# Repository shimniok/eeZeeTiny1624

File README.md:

# eeZeeTiny1624
Developer board for ATtiny1624

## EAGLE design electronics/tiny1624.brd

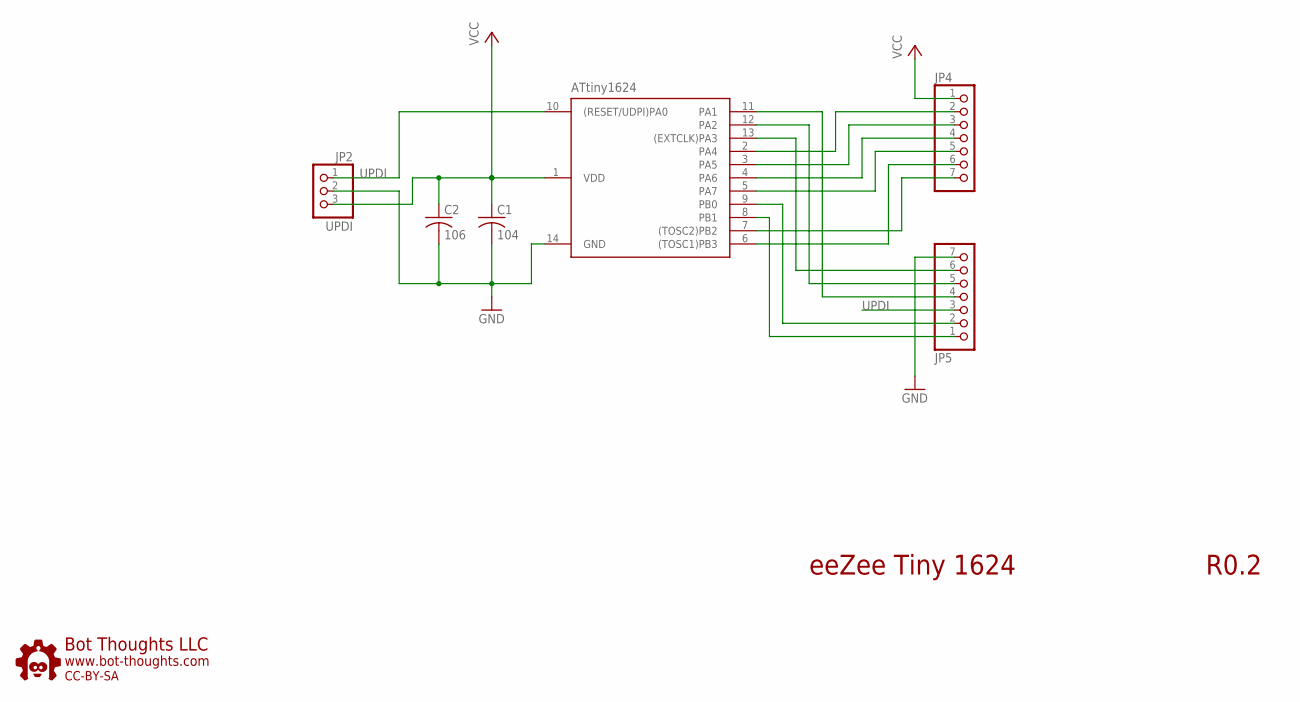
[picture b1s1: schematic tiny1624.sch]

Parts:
C1: 104; C0603; PARTNO 0603YC104KAT2A
C2: 106; 1206; PARTNO MCTT21X106M6R3CT
JP2: UPDI; 1X03-S
JP4, JP5: PINHD-1X07_2.54-S; 1X07-S
U1: ATTINY1624; SOIC14N
U$1: BTLOGO-LOGO-MD; BTLOGOM

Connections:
GND: C1.2, C2.2 (-), JP2.2, JP5.7, U1.14 (GND)
unnamed: JP4.2, U1.2 (PA4)
unnamed: JP4.3, U1.3 (PA5)
unnamed: JP4.4, U1.4 (PA6)
unnamed: JP4.5, U1.5 (PA7)
unnamed: JP4.6, U1.6 ((TOSC1)PB3)
unnamed: JP4.7, U1.7 ((TOSC2)PB2)
unnamed: JP5.1, U1.8 (PB1)
unnamed: JP5.2, U1.9 (PB0)
unnamed: JP5.4, U1.11 (PA1)
unnamed: JP5.5, U1.12 (PA2)
unnamed: JP5.6, U1.13 ((EXTCLK)PA3)
UPDI: JP2.1, JP5.3, U1.10 ((RESET/UDPI)PA0)
VCC: C1.1, C2.1 (+), JP2.3, JP4.1, U1.1 (VDD)

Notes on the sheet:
eeZee Tiny 1624
R0.2

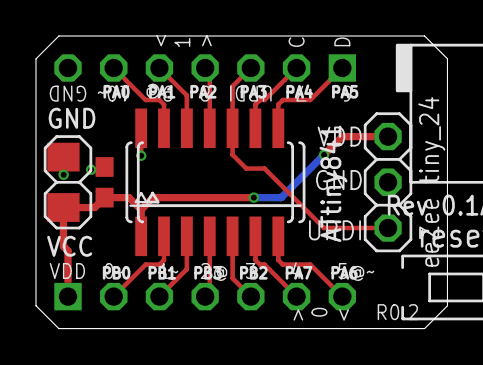
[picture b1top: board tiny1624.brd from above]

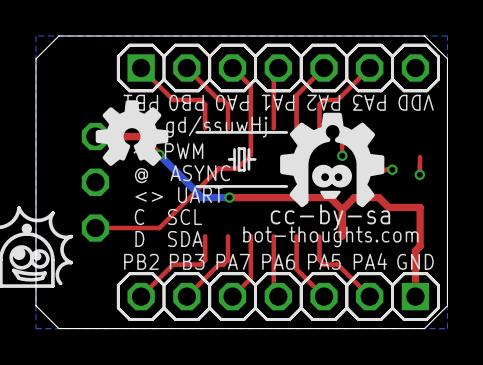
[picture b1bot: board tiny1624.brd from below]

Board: 2 copper layers, 22.9 x 16.3 mm, 7 parts (3 on the bottom side), 14 nets.

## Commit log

2022-03-09 initial version
2022-03-09 updated gerbers
2022-03-09 removed gerbers xln from ignore
2022-03-09 added zip
2022-11-25 Updated reset circuit, added example blink code
2022-11-26 initial fuses documentation
2022-11-26 Removed reset circuit, shrunk board, cleaned up schematic
2022-11-26 Added arduino labeling
2022-11-26 fixed missing updi label
2023-08-19 changed silk to _24
2023-08-19 updated zip

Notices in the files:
electronics/tiny1624.brd:
cc-by-sa
